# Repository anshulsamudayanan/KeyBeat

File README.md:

# KeyBeat

KeyBeat is a mini keyboard which lets the user control their music with ease, with features like volume control, music scrubbing, next and previous song, pause/play, and mute.

## Images

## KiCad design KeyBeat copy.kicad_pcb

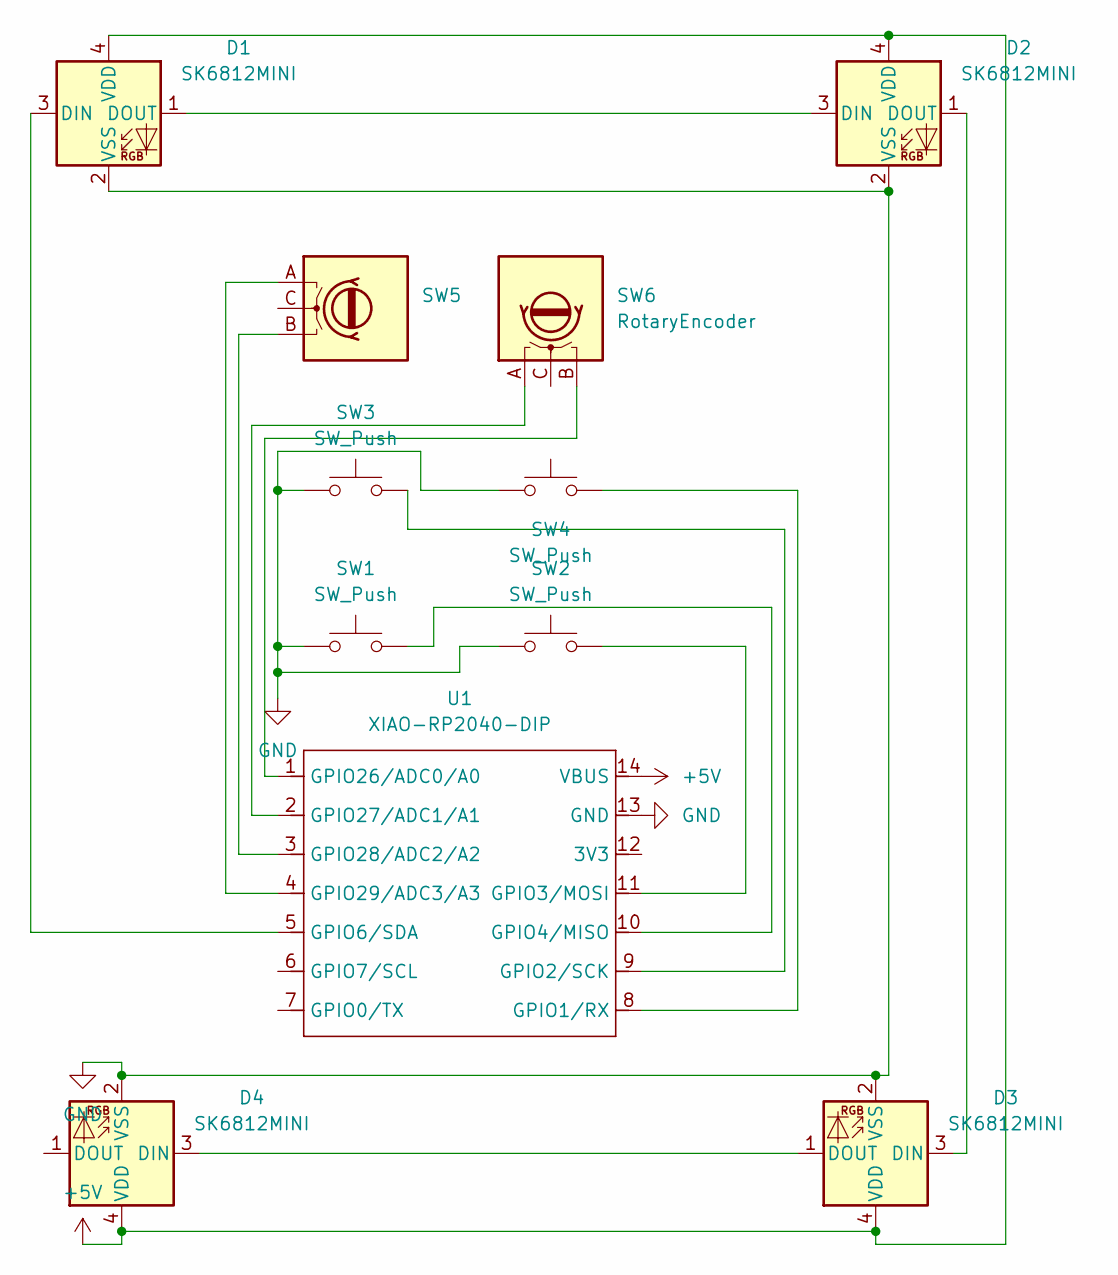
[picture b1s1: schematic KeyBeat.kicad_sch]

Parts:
D1, D2, D3, D4: SK6812MINI; LED_SK6812MINI_PLCC4_3.5x3.5mm_P1.75mm
SW1, SW2, SW3, SW4: SW_Push; SW_Cherry_MX_1.00u_PCB
SW5, SW6: RotaryEncoder; RotaryEncoder_Alps_EC11E-Switch_Vertical_H20mm
U1: XIAO-RP2040-DIP

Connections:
+5V: D1.4 (VDD), D2.4 (VDD), D3.4 (VDD), D4.4 (VDD), U1.14 (VBUS)
GND: D1.2 (VSS), D2.2 (VSS), D3.2 (VSS), D4.2 (VSS), SW1.1, SW2.1, SW3.1, SW4.1, U1.13 (GND)
unnamed: D1.3 (DIN), U1.5 (GPIO6/SDA)
unnamed: D1.1 (DOUT), D2.3 (DIN)
unnamed: D2.1 (DOUT), D3.3 (DIN)
unnamed: D3.1 (DOUT), D4.3 (DIN)
unnamed: SW4.2, U1.8 (GPIO1/RX)
unnamed: SW3.2, U1.9 (GPIO2/SCK)
unnamed: SW2.2, U1.11 (GPIO3/MOSI)
unnamed: SW1.2, U1.10 (GPIO4/MISO)
unnamed: SW6.B, U1.1 (GPIO26/ADC0/A0)
unnamed: SW6.A, U1.2 (GPIO27/ADC1/A1)
unnamed: SW5.B, U1.3 (GPIO28/ADC2/A2)
unnamed: SW5.A, U1.4 (GPIO29/ADC3/A3)

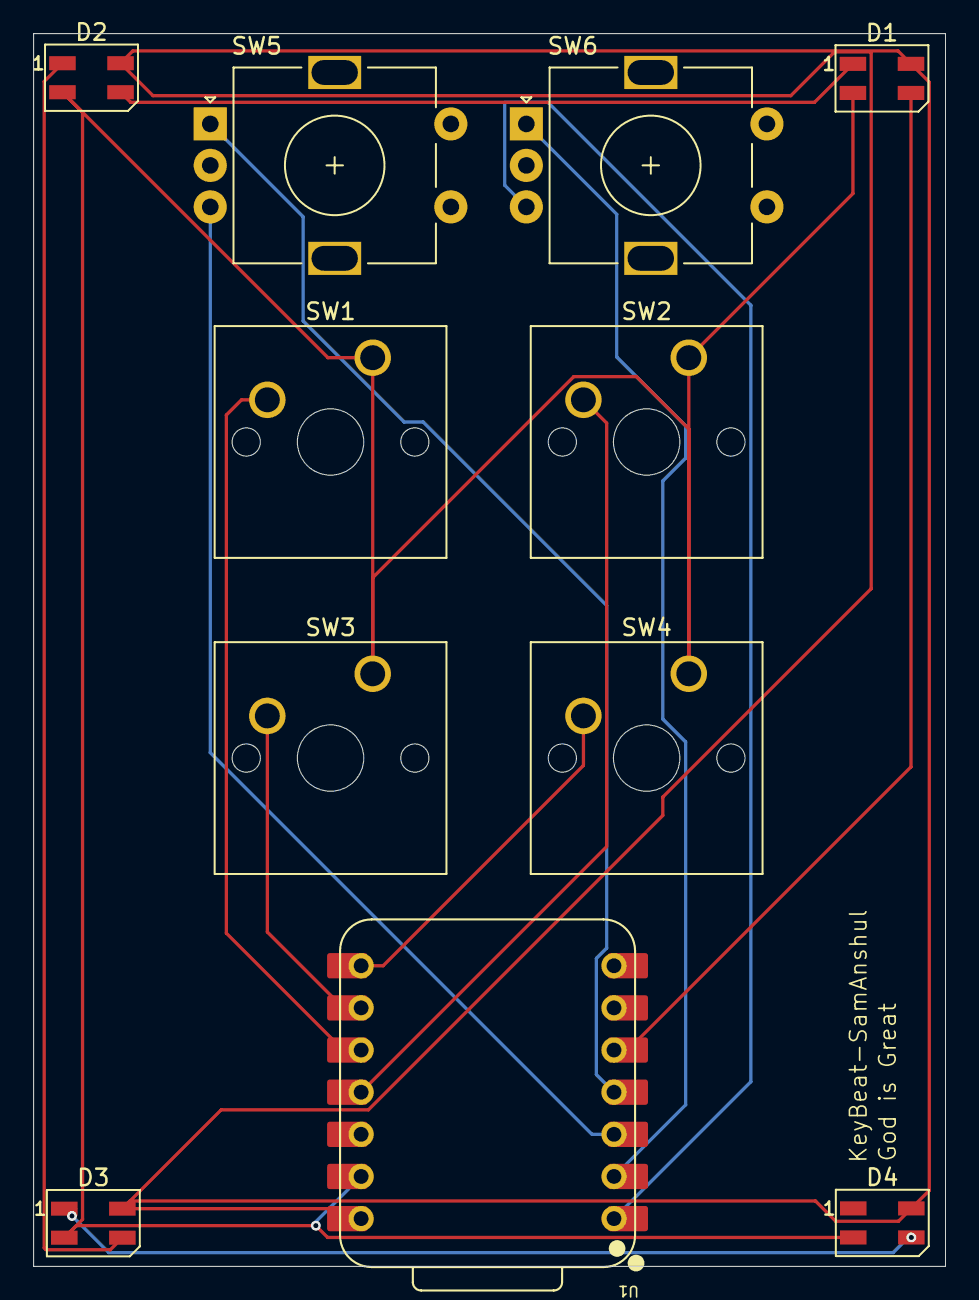
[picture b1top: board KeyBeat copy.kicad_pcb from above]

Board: 2 copper layers, 55.0 x 74.3 mm, 11 parts (0 on the bottom side), 14 nets.

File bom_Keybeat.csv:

Reference,Description,Quantity
PCB,Custom PCB Board,1
D1,SK6812MINI RGB LED,1
D2,SK6812MINI RGB LED,1
D3,SK6812MINI RGB LED,1
D4,SK6812MINI RGB LED,1
U1,Seeed Studio XIAO RP2040,1
SW1,Push Button,1
SW2,Push Button,1
SW3,Push Button,1
SW4,Push Button,1
SW5,Rotary Switch,1
SW6,Rotary Encoder,1
3D_PART_1,3D Printed Component,1
3D_PART_2,3D Printed Component,1
KEYCAP_1,Keycap for Push Button,4
KEYCAP_2,Keycap for Rotary Encoder,2

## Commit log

2025-12-06 Delete Board_Bottom v1.stl
    Going to organize the repo
2025-12-06 Delete Board_Cover v1.stl
    organizing
2025-12-06 Add new Temp file with initial content
2025-12-06 Delete PCB files/Temp
    it was temp
2025-12-06 Create temp
2025-12-06 Enhance README with project details and images
    Updated the README to include a project description and additional images.
